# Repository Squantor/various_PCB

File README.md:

Various prototype PCB's
===========
This repository contains various little boards like level shifters, component breakouts and other simple PCB's. Most of these boards are breadboard plugin friendly and are available at OSH park.
<h1 align="center">Breakouts</h1>
Various breakout boards with additional supporting components to help the application
<h2 align="center">74HCT9046A PLL</h2>
Improved version of the venerable 47HC(T)4046 PLL, main improvement is fixing the deadtime problem with the Flipflop based phase detector and adding a bias resistor for the charge pump output.
<h2 align="center">GTL2003 level shifter</h2>
Bidirectional levelshifter working from 5V on one side to anything lower on the other. Pull up and biasing resistor pads/caps positions included.
<h2 align="center">GTL2003 current mirror/sink</h2>
The GTL2003 bidirectional levelshifter is nothing more then a bunch of N-MOSFETs on a single die with their gates interconnected. Due to close proximity of the FETs to eachother they (should) be reasonably matched well and the datasheet specifies this. Instead of using it for a level shifter application it could also be a multiple channel programmable current sink. Included on the board is a TL431 programmable zener reference with a bunch of resistor pads for biasing the mosfets with a stable voltage.
<h2 align="center">Filament transformer breakout</h2>
Breakout board for the Triad transformer 6.3V, used as a filament transformer for electrostatic CRT's. Going to be used for PM3210 oscilloscope repair.
<h1 align="center">Modules</h1>
<h2 align="center">Transformer module</h2>
Board with flexible transformer layout, bridge rectifier and smoothing caps. Multiple versions.

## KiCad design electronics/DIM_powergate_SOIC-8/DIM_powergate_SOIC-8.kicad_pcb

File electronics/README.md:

Various prototype PCB's
===========
This repository contains various little boards like level shifters, component breakouts and other simple PCB's. Most of these boards are breadboard plugin friendly and are available at OSH park.
* Ikea webcam mount [LED ring PCB](ikea_livecam_leds/README.md) with constant current driver for a LASER pointer

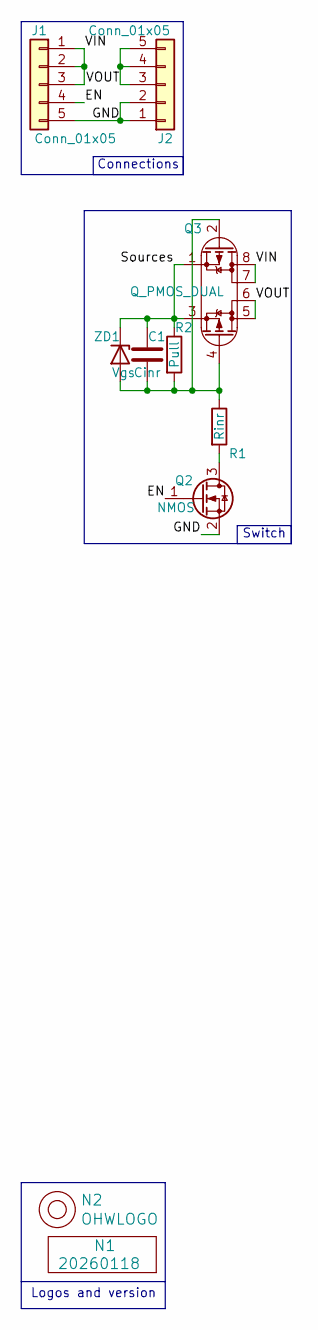
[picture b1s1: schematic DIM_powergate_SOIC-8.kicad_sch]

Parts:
C1: Cinr; C_0603
J1, J2: Conn_01x05; Header-0254-1X05-H010
N1: 20260118; Label_Generic
N2: OHWLOGO; OSHW-Symbol_6.7x6mm_SilkScreen
Q2: NMOS; SOT23-3
Q3: Q_PMOS_DUAL; SOIC-8
R1: Rinr; R_0603_hand
R2: Pull; R_0603_hand
ZD1: Vgs; SOD-323-nexperia-hand

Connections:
/EN: J1.4, Q2.1 (G)
/GND: J1.5, J2.1, J2.2, Q2.2 (S)
/Sources: C1.1, Q3.1 (S1), Q3.3 (S2), R2.1, ZD1.1 (K)
/VIN: J1.1, J1.2, J1.3, Q3.7 (D1), Q3.8 (D1)
/VOUT: J2.3, J2.4, J2.5, Q3.5 (D2), Q3.6 (D2)
unnamed: Q2.3 (D), R1.2
unnamed: C1.2, Q3.2 (G1), Q3.4 (G2), R1.1, R2.2, ZD1.2 (A)

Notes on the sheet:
Logos and version
Connections
Switch

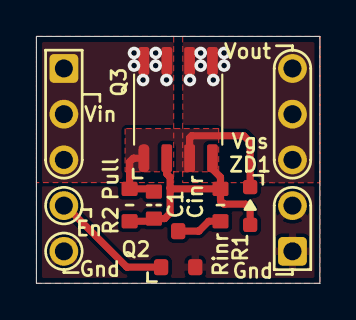
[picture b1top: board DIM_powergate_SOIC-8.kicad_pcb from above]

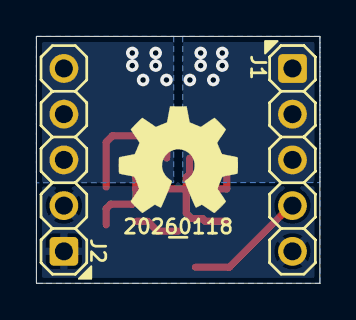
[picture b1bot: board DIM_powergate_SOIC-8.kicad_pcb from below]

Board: 2 copper layers, 15.7 x 13.7 mm, 10 parts (4 on the bottom side), 7 nets.

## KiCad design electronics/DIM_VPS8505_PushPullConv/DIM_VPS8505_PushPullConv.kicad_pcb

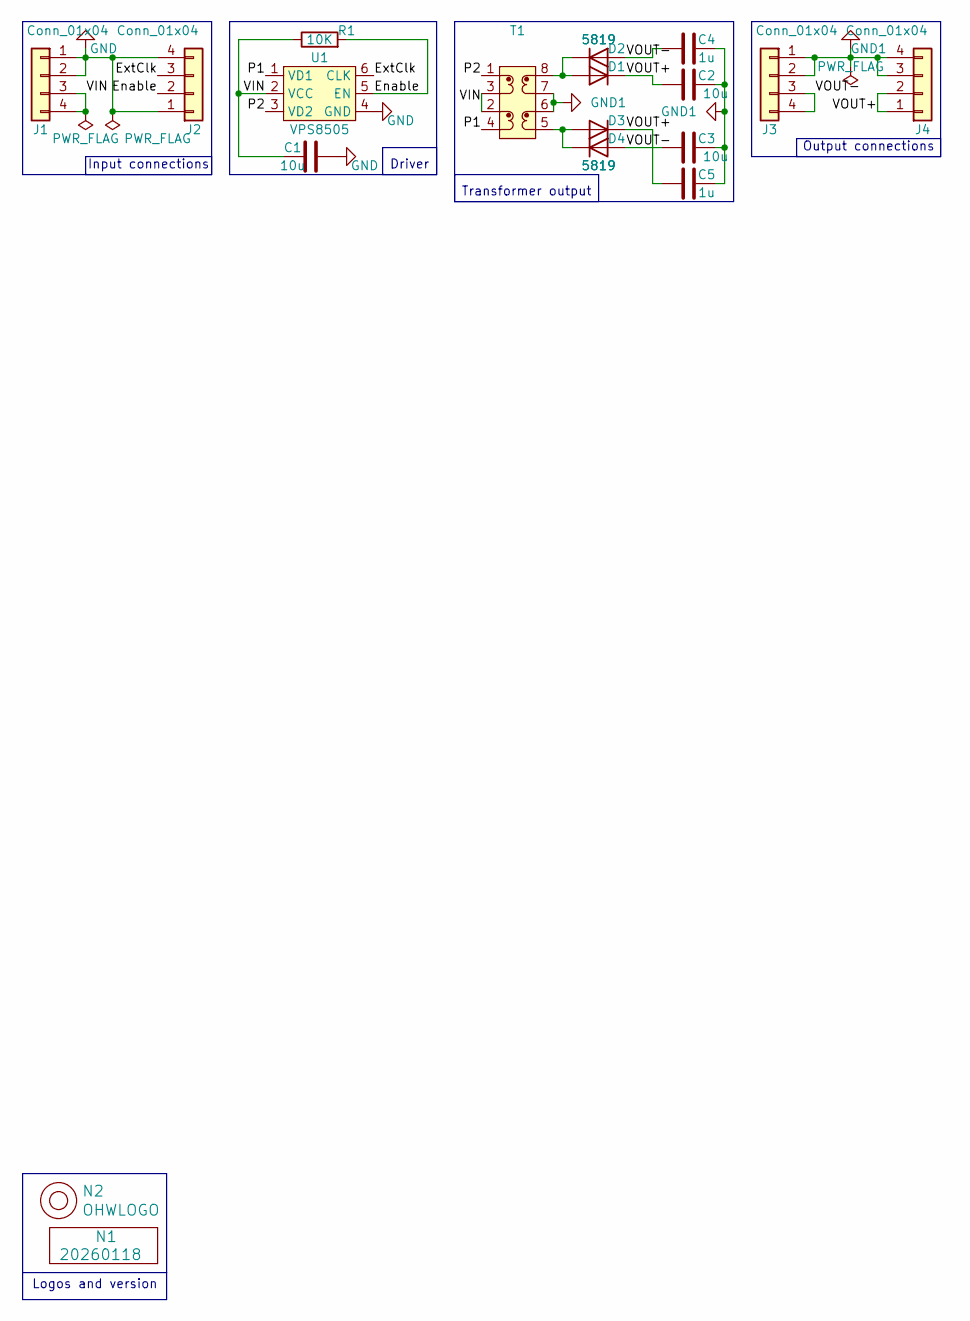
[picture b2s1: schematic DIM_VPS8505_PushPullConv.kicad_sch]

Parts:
C1, C2, C3: 10u; C_1206_0805
C4, C5: 1u; C_0603
D1, D2, D3, D4: 5819; SOD-323HE-shikues
J1, J2, J3, J4: Conn_01x04; Header-0254-1X04-H010
N1: 20260118; Label_Generic
N2: OHWLOGO; OSHW-Symbol_6.7x6mm_SilkScreen
R1: 10K; R_0603_hand
T1: T_2W_8pin_hand
U1: VPS8505; SOT23-6-HAND

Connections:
/Enable: J2.2, R1.2, U1.5 (EN)
/ExtClk: J2.3, U1.6 (CLK)
/P1: T1.4 (N2_2), U1.1 (VD1)
/P2: T1.1 (N1_1), U1.3 (VD2)
/VIN: C1.2, J1.3, J1.4, R1.1, T1.2 (N2_1), T1.3 (N1_2), U1.2 (VCC)
/VOUT+: C2.1, C5.1, D1.1 (K), D3.1 (K), J4.1, J4.2
/VOUT-: C3.1, C4.1, D2.2 (A), D4.2 (A), J3.3, J3.4
GND: C1.1, J1.1, J1.2, J2.1, J2.4, U1.4 (GND)
GND1: C2.2, C3.2, C4.2, C5.2, J3.1, J3.2, J4.3, J4.4, T1.6 (N3_1), T1.7 (N4_2)
unnamed: D1.2 (A), D2.1 (K), T1.8 (N4_!)
unnamed: D3.2 (A), D4.1 (K), T1.5 (N3_2)

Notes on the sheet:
Output connections
Driver
Logos and version
Transformer output
Input connections

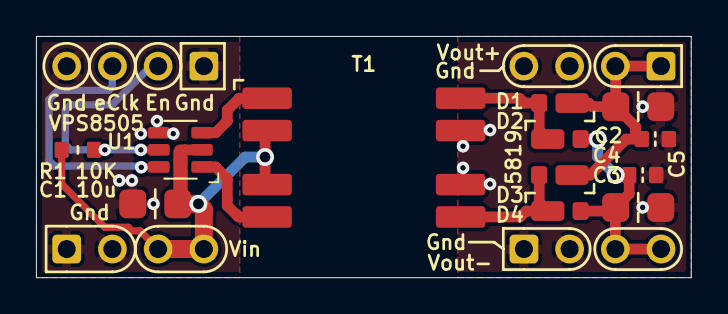
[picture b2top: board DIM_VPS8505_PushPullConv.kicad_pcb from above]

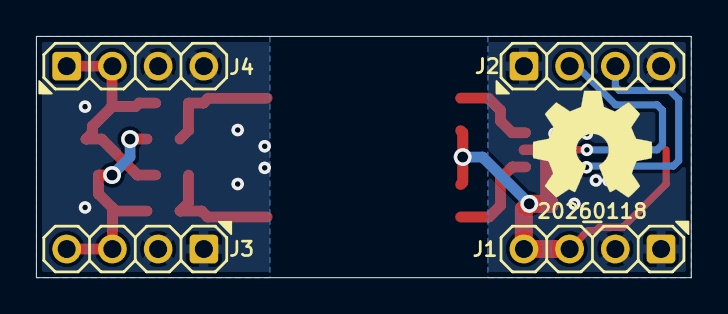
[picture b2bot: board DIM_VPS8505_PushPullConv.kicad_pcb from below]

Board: 2 copper layers, 36.4 x 13.4 mm, 18 parts (6 on the bottom side), 11 nets.

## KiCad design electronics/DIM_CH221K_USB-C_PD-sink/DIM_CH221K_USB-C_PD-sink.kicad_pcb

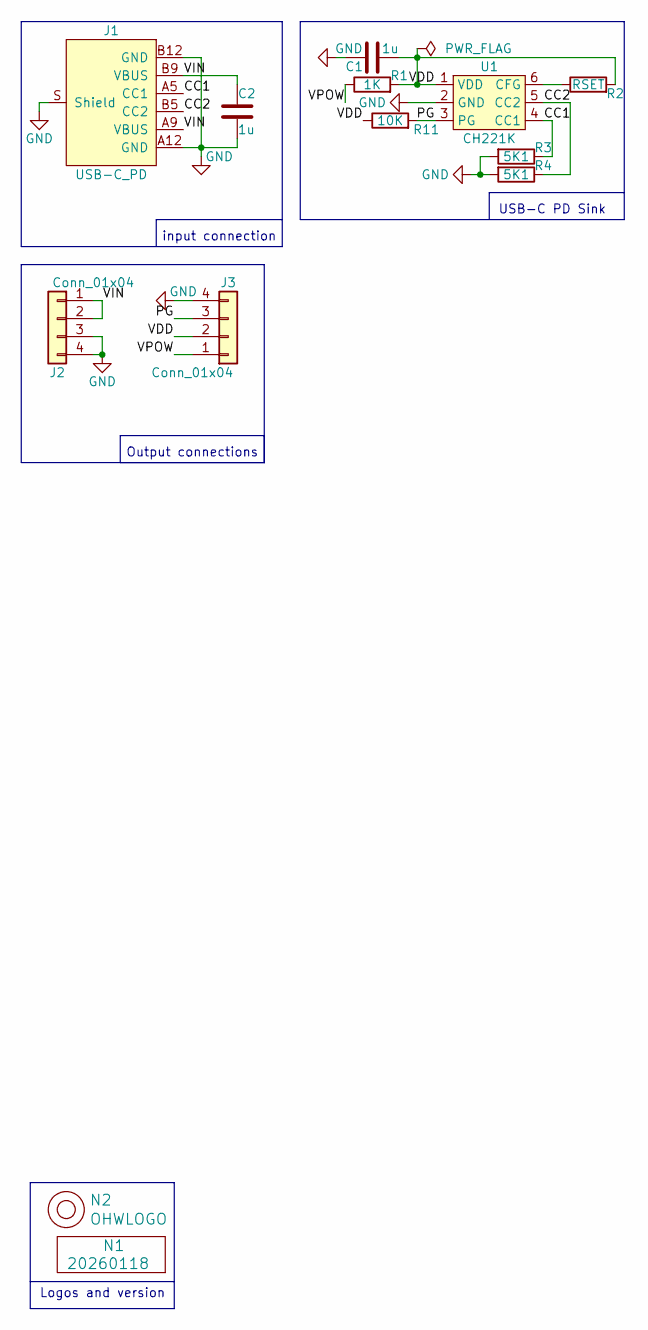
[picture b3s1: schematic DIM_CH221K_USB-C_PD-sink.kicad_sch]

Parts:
C1: 1u; C_0805+0603
C2: 1u; C_1206_0805
J1: USB-C_PD; USB-C-HRO-31-M-17_aisler
J2, J3: Conn_01x04; Header-0254-1X04-H010
N1: 20260118; Label_Generic
N2: OHWLOGO; OSHW-Symbol_6.7x6mm_SilkScreen
R1: 1K; R_0603_hand
R2: RSET; R_0603_hand
R3, R4: 5K1; R_0603_hand
R11: 10K; R_0603_hand
U1: CH221K; SOT23-6-HAND

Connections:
/CC1: J1.A5 (CC1), R3.1, U1.4 (CC1)
/CC2: J1.B5 (CC2), R4.1, U1.5 (CC2)
/PG: J3.3, R11.2, U1.3 (PG)
/VDD: C1.2, J3.2, R1.2, R2.2, R11.1, U1.1 (VDD)
/VIN: C2.1, J1.A9 (VBUS), J1.B9 (VBUS), J2.1, J2.2
/VPOW: J3.1, R1.1
GND: C1.1, C2.2, J1.A12 (GND), J1.B12 (GND), J1.S (Shield), J2.3, J2.4, J3.4, R3.2, R4.2, U1.2 (GND)
unnamed: R2.1, U1.6 (CFG)

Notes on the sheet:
Output connections
input connection
Logos and version
USB-C PD Sink

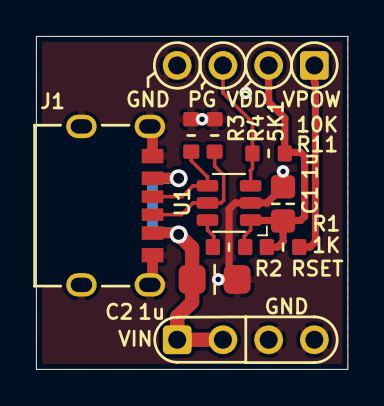
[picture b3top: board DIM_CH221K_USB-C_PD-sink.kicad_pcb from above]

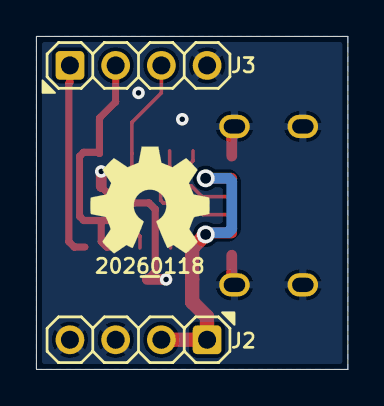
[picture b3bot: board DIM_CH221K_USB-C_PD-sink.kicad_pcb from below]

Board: 2 copper layers, 17.3 x 18.5 mm, 13 parts (4 on the bottom side), 8 nets.

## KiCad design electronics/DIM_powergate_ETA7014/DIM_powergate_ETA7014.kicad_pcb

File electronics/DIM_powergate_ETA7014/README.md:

# Power switch module
Power switch module using the ETA7014 high side switch and overvoltage protection IC.
## TODO's
Still some things need to be done:
* Review with one night in between
* Produce at [Aisler](https://aisler.net/)
* Assemble
* Test & characterise
* update Readme.md with pictures and BOM
## BOM
This is a list of hardware components. 
* [ETA7014](https://www.eta-semi.com/wp-content/uploads/2022/03/ETA7014-V2.1.pdf)
* Some R's C's

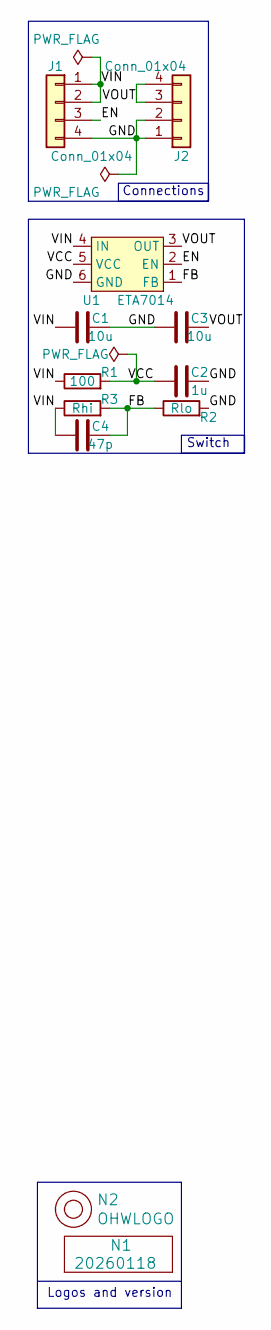
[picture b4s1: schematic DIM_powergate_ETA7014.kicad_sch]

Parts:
C1, C3: 10u; C_0805+0603
C2: 1u; C_0805+0603
C4: 47p; C_0603
J1, J2: Conn_01x04; Header-0254-1X04-H010
N1: 20260118; Label_Generic
N2: OHWLOGO; OSHW-Symbol_6.7x6mm_SilkScreen
R1: 100; R_0603_hand
R2: Rlo; R_0603_hand
R3: Rhi; R_0603_hand
U1: ETA7014; SOT23-6-HAND

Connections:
/EN: J1.3, U1.2 (EN)
/FB: C4.2, R2.1, R3.2, U1.1 (FB)
/GND: C1.2, C2.2, C3.1, J1.4, J2.1, J2.2, R2.2, U1.6 (GND)
/VCC: C2.1, R1.2, U1.5 (VCC)
/VIN: C1.1, C4.1, J1.1, J1.2, R1.1, R3.1, U1.4 (IN)
/VOUT: C3.2, J2.3, J2.4, U1.3 (OUT)

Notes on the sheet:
Logos and version
Connections
Switch

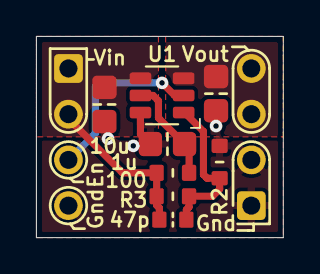
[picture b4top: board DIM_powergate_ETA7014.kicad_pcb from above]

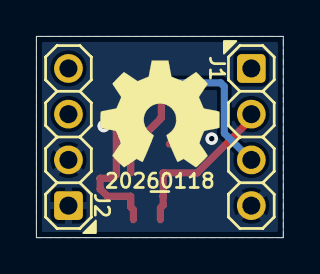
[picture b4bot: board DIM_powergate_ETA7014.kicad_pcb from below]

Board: 2 copper layers, 13.7 x 11.2 mm, 12 parts (4 on the bottom side), 6 nets.

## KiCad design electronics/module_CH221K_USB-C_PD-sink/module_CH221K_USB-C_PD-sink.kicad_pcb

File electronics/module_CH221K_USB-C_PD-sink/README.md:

# CH221K USB PD sink module
USB PD sink based on CH221K chip. Similar to many aliexpress boards but contains a power good indicator and power good power on switch to switch on power when negotation has completed.
## TODO's
Still some things need to be done:
* schematic entry (WIP)
* PCB layout (WIP)
* Review with one night in between
* Produce
* Assemble
* Test & characterise
* update Readme.md with pictures and BOM
## BOM
* [CH221K](https://www.wch-ic.com/products/CH224.html) from LCSC or Aliexpress
* SOT-23 P channel fet
* 8V zener in SOD323 for PG pin protection
* Vgate zener in SOD323 for Pchannel switch protection

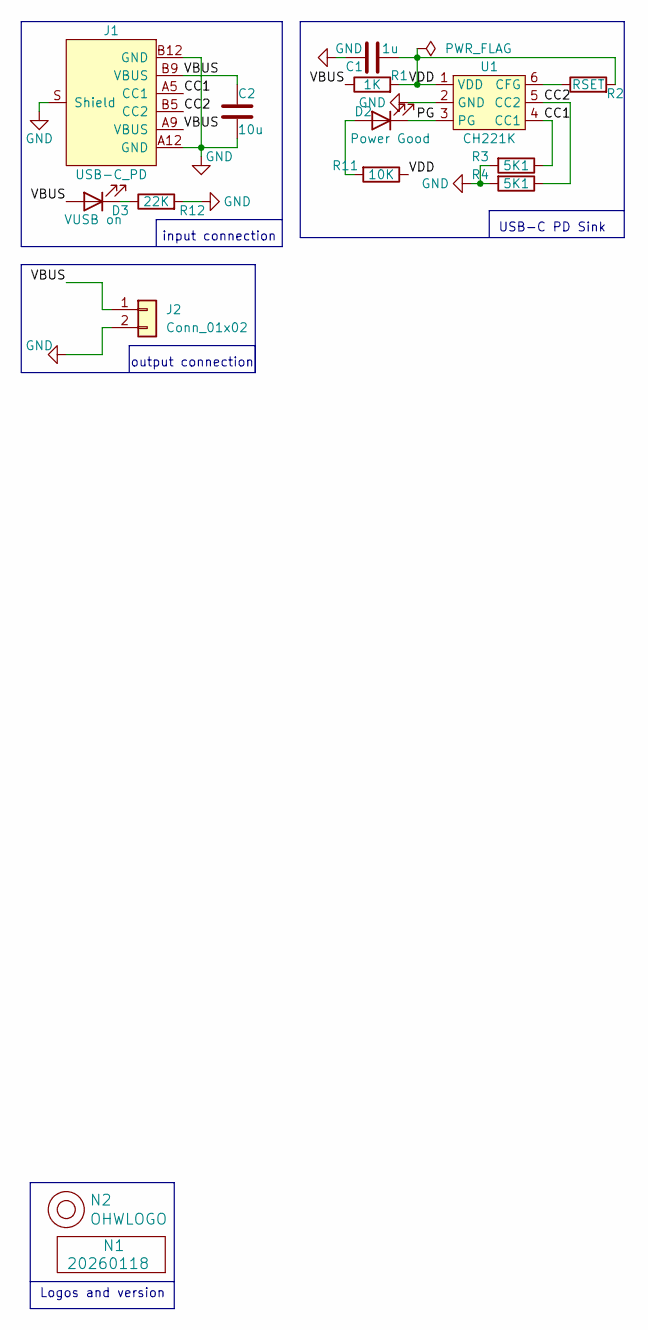
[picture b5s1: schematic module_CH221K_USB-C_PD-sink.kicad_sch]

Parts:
C1: 1u; C_0805+0603
C2: 10u; C_1206_0805
D2: Power Good; LED_0603_hand
D3: VUSB on; LED_0603_hand
J1: USB-C_PD; USB-C-HRO-31-M-17_aisler
J2: Conn_01x02; JST_XH_S2B-XH-A-1_1x02_P2.50mm_Horizontal
N1: 20260118; Label_Generic
N2: OHWLOGO; OSHW-Symbol_6.7x6mm_SilkScreen
R1: 1K; R_0603_hand
R2: RSET; R_0603_hand
R3, R4: 5K1; R_0603_hand
R11: 10K; R_0603_hand
R12: 22K; R_0603_hand
U1: CH221K; SOT23-6-HAND

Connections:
/CC1: J1.A5 (CC1), R3.1, U1.4 (CC1)
/CC2: J1.B5 (CC2), R4.1, U1.5 (CC2)
/PG: D2.1 (K), U1.3 (PG)
/VBUS: C2.1, D3.2 (A), J1.A9 (VBUS), J1.B9 (VBUS), J2.1, R1.1
/VDD: C1.2, R1.2, R2.2, R11.1, U1.1 (VDD)
GND: C1.1, C2.2, J1.A12 (GND), J1.B12 (GND), J1.S (Shield), J2.2, R3.2, R4.2, R12.2, U1.2 (GND)
unnamed: D2.2 (A), R11.2
unnamed: D3.1 (K), R12.1
unnamed: R2.1, U1.6 (CFG)

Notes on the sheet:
input connection
Logos and version
output connection
USB-C PD Sink

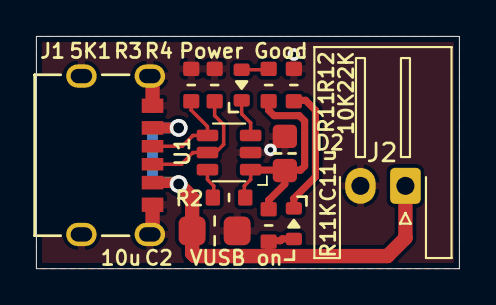
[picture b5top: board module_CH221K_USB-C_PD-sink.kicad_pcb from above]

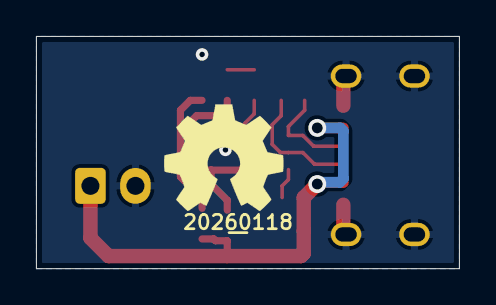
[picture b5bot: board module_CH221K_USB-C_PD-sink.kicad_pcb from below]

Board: 2 copper layers, 23.5 x 12.9 mm, 15 parts (2 on the bottom side), 9 nets.

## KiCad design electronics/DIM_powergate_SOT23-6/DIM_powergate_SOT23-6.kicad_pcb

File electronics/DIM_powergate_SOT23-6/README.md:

# Power switch module
Simple power switch module with a dual PMOS and NMOS FET with some additional components. Rpull is the pullup resistor used for the PMOS gate. Rinr and Cinr are a RC network that will limiting inrush current. Be aware that the inrush limiting will also prolong the period that the PMOS FET is in its resistive regime and may dissipate a lot of heat. Be aware that SOT23-6 dual PMOS devices have a non reversible pinout than most SOT363 SOT536 dual mosfets.
## TODO's
Still some things need to be done:
* Review with one night in between
* Produce at [Aisler](https://aisler.net/)
* Assemble
* Test & characterise
* update Readme.md with pictures and BOM
## BOM
This is a list of hardware components. 
* Any SOT23-6 Dual PMOS FET matching your current/voltage characteristics
* Any SOT23 NMOS FET for switching the PMOS gate, be aware of the maximum voltage being switched
* Zener diode for gate protection, depending on maximum Vgate of the PMOS FET
* Some R's C's

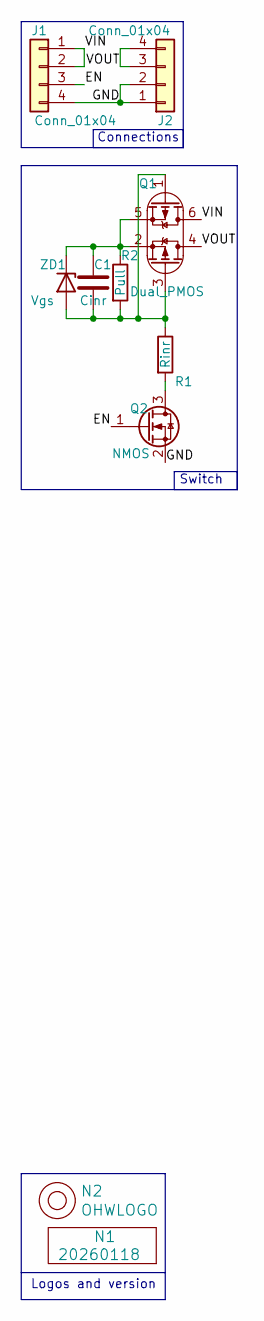
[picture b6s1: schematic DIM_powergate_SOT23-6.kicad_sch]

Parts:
C1: Cinr; C_0603
J1, J2: Conn_01x04; Header-0254-1X04-H010
N1: 20260118; Label_Generic
N2: OHWLOGO; OSHW-Symbol_6.7x6mm_SilkScreen
Q1: Dual_PMOS; SOT23-6-HAND
Q2: NMOS; SOT23-3
R1: Rinr; R_0603_hand
R2: Pull; R_0603_hand
ZD1: Vgs; SOD-323-nexperia-hand

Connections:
/EN: J1.3, Q2.1 (G)
/GND: J1.4, J2.1, J2.2, Q2.2 (S)
/VIN: J1.1, J1.2, Q1.6 (D1)
/VOUT: J2.3, J2.4, Q1.4 (D2)
unnamed: C1.2, Q1.1 (G1), Q1.3 (G2), R1.1, R2.2, ZD1.2 (A)
unnamed: C1.1, Q1.2 (S2), Q1.5 (S1), R2.1, ZD1.1 (K)
unnamed: Q2.3 (D), R1.2

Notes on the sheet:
Logos and version
Connections
Switch

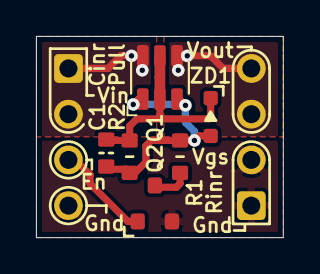
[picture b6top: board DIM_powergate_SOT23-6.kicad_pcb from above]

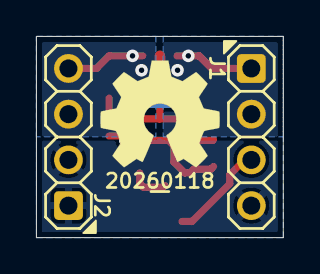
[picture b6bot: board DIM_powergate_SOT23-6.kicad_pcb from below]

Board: 2 copper layers, 13.7 x 11.2 mm, 10 parts (4 on the bottom side), 7 nets.

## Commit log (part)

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2021-03-21 forgot footprint definition for inductor
2021-03-21 placed and routed
2021-03-21 reviewed little logic SOT353 PCB
2021-03-21 reviewed SSR module
2021-04-01 WIP readme update
2021-04-01 further expanded readme and documentation
2021-04-01 fixed incorrect link to picture
2021-04-01 added frequencies to example table
2021-04-14 changed boostcap size, changed high current path to use multiple smaller vias
2021-04-16 different SSR's needed
2021-04-17 optimized placement of components to be more compact
2021-04-17 updated high power SSR with more compact components
2021-04-17 routed more compact components
2021-04-17 silk changes
2021-04-17 started with SY8291ABC breakout
2021-04-17 modified, layedout, and completed, now wait one day in between
2021-04-18 added additional current label, optimized some track placement
2021-04-18 added type of SSR label, fixed incorrect resistor value, updated versionnumber
2021-04-18 changed name of optotriac to generic name, the type field will tell what type of SSR it is
2021-04-18 updated versionnumber, changed optotriac name, added SSR type label, added cutouts near mounting holes and pins at potential
2021-04-19 updated versionnumber, removed one input capacitor, made design more compact, removed solder mask under IC for better cooling, added PCB title, changed Vout label
2021-04-19 updated versionnumber, fixed DRC errors
2021-04-19 added soldermask keepout, DRC errors fixed, title added, changed Vout Iout labels
2021-04-20 updated versionnumber, changed copper planes to have bigger spacing values, optimized ground planes a bit
2021-04-21 changed indicator power led, changed inductor size, enlarged PCB a bit
2021-04-22 updated versionnumber, changed coil sizes
2021-04-22 updated versionnumbers, added pin labels
2021-04-22 updated coil size, some component position optimizations
2021-04-23 changed some trace positions to have more distance from other potentials
2021-04-23 updated versionnumber, minor silk changes
2021-04-23 added current label, minor silk moves
2021-04-23 am forgot component labeling
2021-04-24 added picture of the CH340E module
2021-06-07 added initial USB-C PD only breakout
2021-06-07 updated with some USB-C connectors
2021-06-08 added LED indicator and breakout connector
2021-06-08 updated library with fixed USB-C PD connector
2021-06-08 ERC passed
2021-06-08 changed pin assignment on breakout to ease routing
2021-06-08 added additional 5mm led
2021-06-08 routed all the traces
2021-06-09 added on PCB USB-C connector
2021-06-09 changed LED series resistor to 0603
2021-06-09 copied over USB-C PD only breakout to new project
2021-06-09 changed USB-C connector
2021-06-10 minor copper changes, added pin labels
2021-06-10 added breakout, testpins, updated TODO's
2021-06-10 routed and silk placement completed
2021-06-10 started with CH340E with USB-C module
2021-06-10 placement fixed with on PCB USB-C breakout
2021-06-10 added regulator, changed resistor assignments
2021-06-11 created usb-C filter
2021-06-11 updated usb output schematic symbol
2021-06-12 updated versionnumber
2021-06-12 updated versionnumber, usb data lines routing improved, led position and test pads updated
2021-06-12 updated versionnumber, optimized differential pairs, silk placement improved
2021-06-12 updated todo, updated versionnumber
2021-06-12 silk and led position optimization
2021-06-12 seems that I actually worked on the CH340B USB breakout
2021-06-12 changed to CH340E and started routing/layout
2021-06-13 changed regulator to SOT23 lower cost regulator, updated versionnumber, put versionnumber and mechanical in seperate box
2021-06-13 added box
2021-06-13 routed SOT-23 regulator
2021-06-13 updated versionnumber, silk movement
2021-06-13 updated versionnumber, optimized some component placement
2021-06-13 updated versionnumber, added additional led to show usb output power, added jumper to separate the two power domains, changed led positioning
2021-06-13 renaming project names, seem they kept their origin project names!
2021-06-29 added USB-C breakout box 3d model as a copy from the hammond 1551M
2021-07-01 added USB-C hole to the box
2021-07-02 added opening for header connectors
2021-09-05 fixed usb A out schematic symbol
2021-09-05 updated versionnumber, fixed schematic component, some changes here and there on PCB
2021-09-05 bus link jumper to 0805 size due to higher currents
2021-09-05 routed and fixed error in board
2021-09-13 started sharp memory LCD breakout
2021-09-13 started with low power oscillator test
2021-09-13 initial schematic
2021-09-14 WIP schematic
2021-09-24 initial schematic with just connections
2021-09-24 started with inital layout
2021-09-25 added stabistor
2021-09-25 small changes
2021-09-26 added crystal footprint, passing ERC, updated versionnumber
2021-09-26 placing, routing, added decoupling capacitor, placing silk
2021-09-27 added TODO's
2021-09-27 added extra ground plane to PCB, added REG710 step up converter
2021-09-27 forgot resistor footprint
2021-09-28 changed regulator setup, updated versionnumber
2021-09-28 moved pinning of board, placed, and routed everything
2021-09-28 added extra ground testpoint near signal for easy measurements
2021-09-29 trying to add a TVS diode
2021-09-30 placed and routed TVS diode array, updated silk
2021-09-30 fixed mistake, missing resistor on DISP
2021-10-01 final checks before production
2021-10-01 final check before production
2021-10-12 minor silk changes
2021-10-12 updated version number and TODO
2021-10-12 few extra gnd vias
2021-10-12 changed one component value label to align better
2021-10-13 started with breakout for kailh choc buttons
2021-10-13 created keymatrix and initial placement
2021-10-15 modified keypad demo with simple pins
2021-10-15 added additional diode footprints
2021-10-15 routing completed, changed pinout to ease routing
2021-10-15 silk placement completed
2021-10-15 updated BOM
2021-10-15 started with 3 switch kailh breakout
2021-10-15 newer PCB library
2021-10-15 work in progress on schematic of 3 button kailh choc button breakout
2021-10-15 started with 4 switch kailh choc frontplate
2021-10-15 finished PCB
2021-10-15 copied 4 switch plate to 3 switch
2021-10-16 imported plate PCB to make sure we have the same dimensions
2021-10-16 routed and placed silk
2021-10-18 resizing PCB and different mounting method
2021-10-18 changed hole plate to smaller PCB so it can be tiled
2021-10-19 updated physical dimensions for 3 button choc frontplate
2021-10-19 moved connectors
2021-10-19 changed connector positions
2021-11-02 updated library
2021-11-03 place&route&silk position completed
2021-11-03 updated status
2021-11-07 schematic and routing completed
2021-11-07 renamed SOT363 breakout, as SOT is an abbreviation after all
2021-11-07 started with SOT457 breakout
2021-11-07 completed SOT457 breakout
2021-11-07 updated design status
2021-11-10 parking SOT666 breakout, not producable by oshpark
2021-11-10 moved some traces
2021-11-15 removed unproducable by oshpark project
2022-02-16 changed JST connectors to edge connectors, changed switch pitch
2022-02-16 updated 4 button breakout kailh switches
2022-03-22 added breakout for polulu 16 pin stepper motor driver
2022-03-22 further updates to breakout
2022-04-20 started with netfilter module
2022-04-21 assigned footprints from new PCB library
2022-04-21 added wurth library
2022-07-18 added test mainboard for a 10*10cm aluminium box
2022-07-18 added kicad6 ignorables
2022-07-18 inital mainboard test layout
2022-07-24 further connector placement
2022-07-25 further routing of busses, but blocked now
2022-08-29 updated footprints, silk placements
2022-09-16 alubox mainboard
2022-09-23 created board raspberry pi pico SWD breakout
2022-09-23 changed connector so we have silk space for versionnumber and date code
2022-09-23 updated to have power LED, silk placement, board layouted
2022-11-28 started with the SG1 strapubox template
2022-11-28 WIP schematic entry and component+footprint definitions
2022-11-29 WIP rectifier section
2022-11-30 WIP further development
2022-12-01 routing completed WIP silk placement
2023-02-11 updated cutout sizes
2023-02-11 added mounting hole definitions (forgot to add
2023-02-11 added small fixes, through wire holes
2023-04-09 redid board but with proper hole spacing and more flexible sizing
2023-04-09 fixed ERC errors
2023-04-10 WIP adding front LED and power switches
2023-04-11 further updates and additions to switch and leds
2023-04-14 place and route LED and switches
2023-04-15 fixed error with power switch pinout
2023-04-16 further routing
2023-04-17 updated pinouts
2023-04-18 routed new voltage rails
2023-05-05 started with alubox powersupply
2023-05-05 fixed board outline
2023-05-05 updated schematic with lessons learned
2023-05-05 forgot to save schematic
2023-05-05 minor positioning
2023-05-07 small outline adjustment to fit adapter box better
2023-05-13 added input switching connectors
2023-05-13 further changes of decoupling of AC inputs
2023-05-14 WIP PSU circuits
2023-05-19 further added PSU parts and fixed output regulator
2023-05-19 minor schematic fixes and errors
2023-05-19 further net shifts, changing component footprints to better fit
2023-05-19 WIP placing parts around regulators
2023-05-21 WIP component placement
2023-05-21 fixed power supply rail names
2023-05-23 Routing completed, WIP silk placement
2023-05-23 WIP silk placement
2023-05-27 reorganizing schematic
2023-05-27 added small regions for diodes to cool
2023-05-27 ERC passes, added powerflags
2023-05-27 fixed DRC errors
2023-05-28 changed jack connectors to use holed jacks
2023-05-28 minor optimizations
2023-05-28 placed and routed capacitors
2023-05-28 fixed small issue that aisler reported
2023-05-30 fixed aisler problems
2023-06-13 added 10x10 alubox drillguide
2023-06-19 added pin labels
2023-06-30 updated to kicad 7
2023-06-30 changed diode footprints, fixed LM337 footprint
2023-07-07 routing completed, placing silk
2023-07-16 Added electronics specific gitignore
2023-07-16 silk placement done, more optimizations on traces and cooling planes
2023-09-15 project changes
2023-09-15 updated drilling guide
2023-09-15 updated adapter and reviewed
2023-09-15 updated alubox PSU
2024-04-25 added white only neopixel sized led board
2024-05-24 added tiled PCB
2024-05-25 updated SOT457 breakout to kicad7 and added some parts
2024-05-26 panelized SOT457
2024-05-30 ready for production
2024-06-07 updated low power oscillator to kicad 7
2024-07-05 updated labels
2024-07-05 added WS2813 style LED
2024-07-05 removed old kailh switch breakouts
2024-07-05 started with small keypad test modules
2024-07-06 updated to newer kicad version
2024-07-08 changed/removed names
2024-07-08 fixing silk overlaps
2024-07-12 production run, updated versionnumbers, added tiled versions
2024-07-14 update to kicad 8
2024-07-16 minor updates
2024-07-17 small kicad 8 updates
2024-09-15 forgotten some data
2024-12-20 forgotten updates
2024-12-20 library update
2025-01-13 created SOT i2C EEPROM
2025-01-24 added EEPROM SOIC breakout
2025-01-24 updated and changed sharp memory lcd breakout
2025-03-23 preparation for production
2025-04-01 added tiled PCB's
2025-04-06 Work in progress CH224K USB-PD sink module
2025-05-02 updated parts things
2025-05-02 WIP ikea livecam LEDS mount
2025-05-02 added pick and place machine origin
2025-05-04 layout of LED's
2025-05-05 Place and route completed, WIP silk placement
2025-05-07 review and small changes
2025-05-11 review done of livecam
2025-06-01 added some documentation to IKEA webcam mount led ring
2025-07-29 fixed issues and simplified
2025-10-02 Added DIP CH221K breakout
2025-10-03 added SN6505 pushpull converter module
2025-10-04 renamed SN6505 module
2025-10-04 WIP VPS8701 module
2026-01-02 library update, silk labels added
2026-01-03 Added DIM module, simple SOT23 PMOS power switch
2026-01-04 small changes to CH221K with redundant components and adding labels
2026-01-04 changed label of CH221K power pin
2026-01-04 added SOIC-8 powergate
2026-01-08 fixing DRC/ERC warnings/errors
2026-01-09 renamed and cleaned up SN6505 breakout
2026-01-09 ERC/DRC fixed, small silk labels added
2026-01-09 Updated VPS8701 DIM, fixed ERC/DRC
2026-01-11 added new Power gate test PCB based on the ETA7014 powerswitch and protector
